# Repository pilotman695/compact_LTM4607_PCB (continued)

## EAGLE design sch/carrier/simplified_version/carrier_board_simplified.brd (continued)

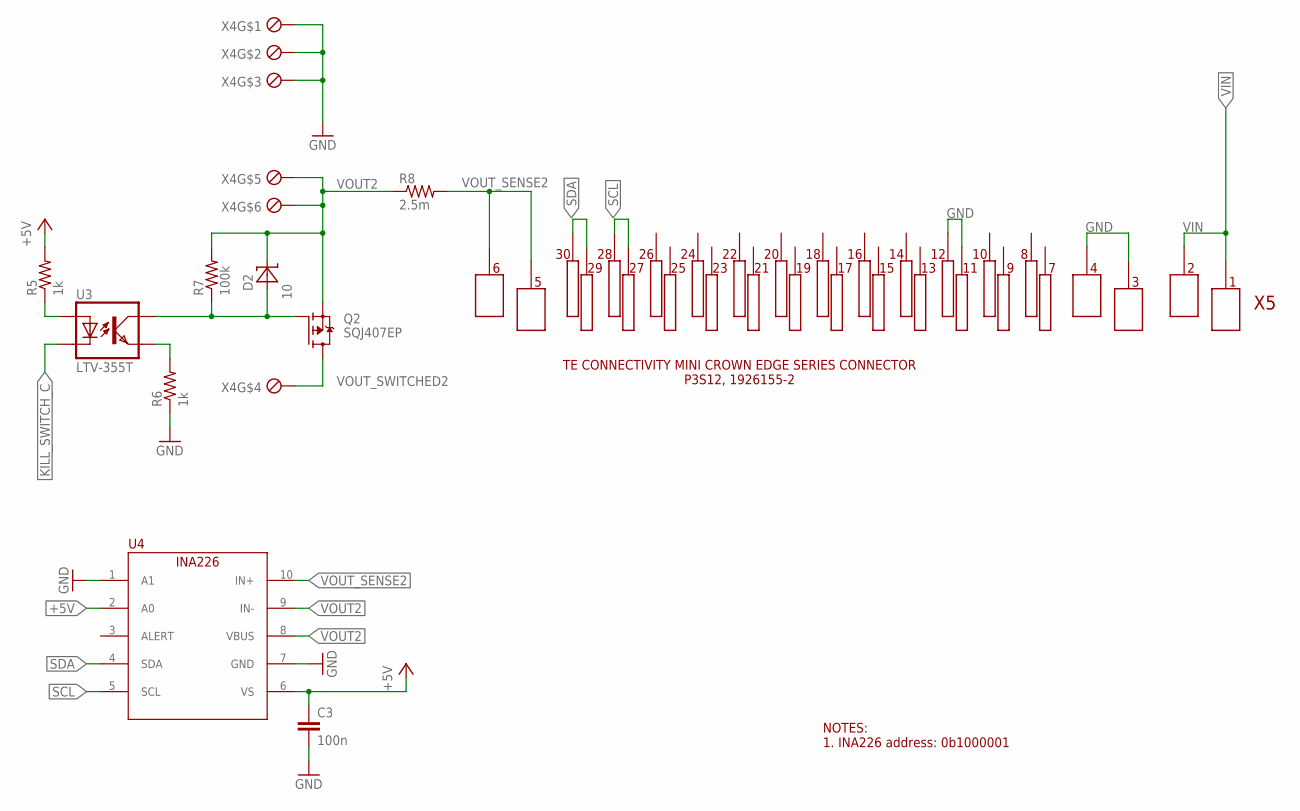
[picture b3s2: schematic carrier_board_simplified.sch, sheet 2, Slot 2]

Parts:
C3: 100n; C0603
D2: 10; SOD123
Q2: SQJ407EP; POWERPAK_SO8L_SINGLE
R5, R6: 1k; R0603
R7: 100k; R0603
R8: 2.5m; R2512
U3: LTV-355T; SMD4
U4: INA226; MSOP10
X4: 284391-6
X5: 1926155-2_SOCK

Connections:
+5V: C3.1, R5.2, U4.2 (A0), U4.6 (VS); also elsewhere on the board
GATE_VOUT2: D2.2 (A), Q2.P$4 (G), R7.1, U3.COLLECTOR (COL)
GND: C3.2, R6.1, U4.1 (A1), U4.7 (GND), X4.P$1, X4.P$2, X4.P$3, X5.P$3_1, X5.P$3_2, X5.P$3_3, X5.P$4_1, X5.P$4_2, X5.P$4_3, X5.P$11, X5.P$12; also elsewhere on the board
KILL_SWITCH_C: U3.CATHODE (C); also elsewhere on the board
unnamed: R6.2, U3.EMITTER (EMIT)
unnamed: R5.1, U3.ANODE (A)
SCL: U4.5 (SCL), X5.P$27, X5.P$28; also elsewhere on the board
SDA: U4.4 (SDA), X5.P$29, X5.P$30; also elsewhere on the board
VIN: X5.P$1_1, X5.P$1_2, X5.P$1_3, X5.P$2_1, X5.P$2_2, X5.P$2_3; also elsewhere on the board
VOUT2: D2.1 (C), Q2.P$1 (S), Q2.P$2 (S), Q2.P$3 (S), R7.2, R8.1, U4.8 (VBUS), U4.9 (IN-), X4.P$5, X4.P$6
VOUT_SENSE2: R8.2, U4.10 (IN+), X5.P$5_1, X5.P$5_2, X5.P$5_3, X5.P$6_1, X5.P$6_2, X5.P$6_3
VOUT_SWITCHED2: Q2.P$5 (D), Q2.P$6 (D), Q2.P$7 (D), Q2.P$8 (D), X4.P$4

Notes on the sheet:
NOTES: 1. INA226 address: 0b1000001

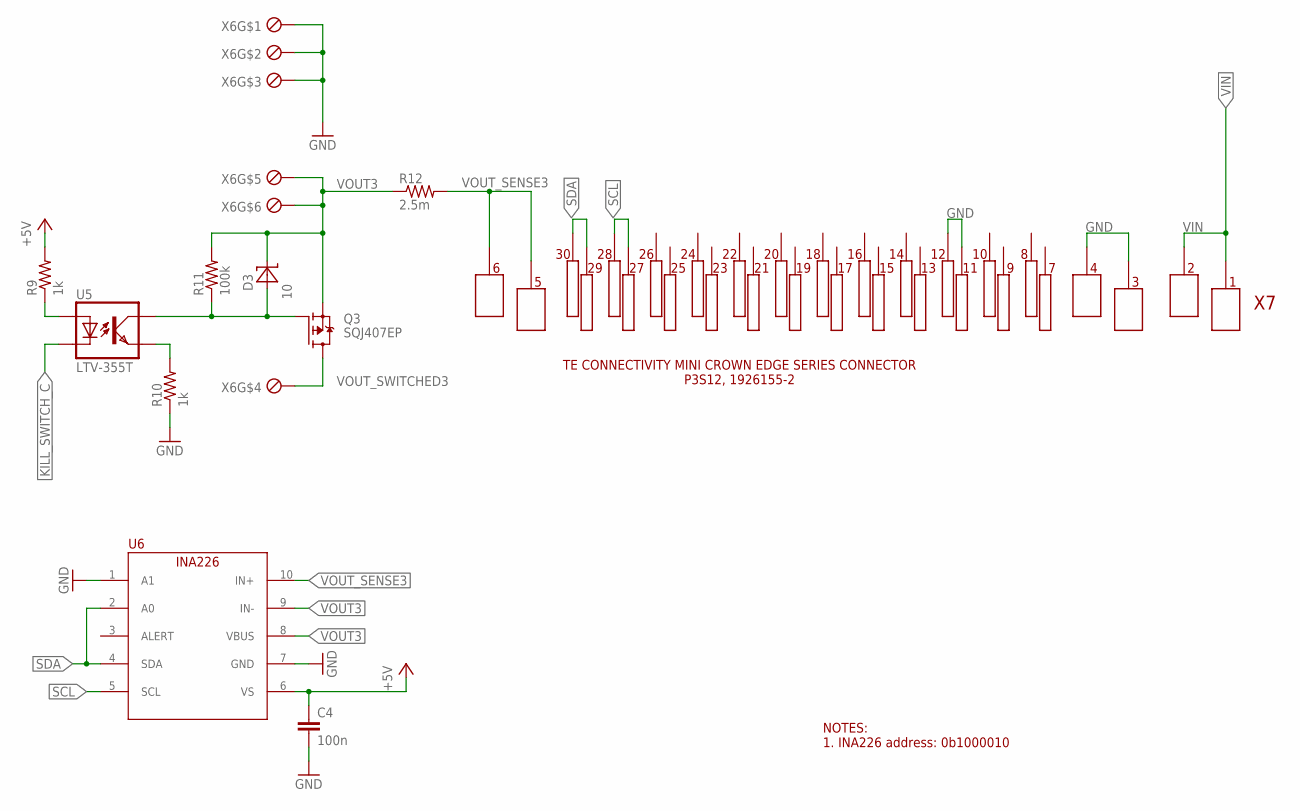
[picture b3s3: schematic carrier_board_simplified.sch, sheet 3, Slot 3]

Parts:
C4: 100n; C0603
D3: 10; SOD123
Q3: SQJ407EP; POWERPAK_SO8L_SINGLE
R9, R10: 1k; R0603
R11: 100k; R0603
R12: 2.5m; R2512
U5: LTV-355T; SMD4
U6: INA226; MSOP10
X6: 284391-6
X7: 1926155-2_SOCK

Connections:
+5V: C4.1, R9.2, U6.6 (VS); also elsewhere on the board
GATE_VOUT3: D3.2 (A), Q3.P$4 (G), R11.1, U5.COLLECTOR (COL)
GND: C4.2, R10.1, U6.1 (A1), U6.7 (GND), X6.P$1, X6.P$2, X6.P$3, X7.P$3_1, X7.P$3_2, X7.P$3_3, X7.P$4_1, X7.P$4_2, X7.P$4_3, X7.P$11, X7.P$12; also elsewhere on the board
KILL_SWITCH_C: U5.CATHODE (C); also elsewhere on the board
unnamed: R10.2, U5.EMITTER (EMIT)
unnamed: R9.1, U5.ANODE (A)
SCL: U6.5 (SCL), X7.P$27, X7.P$28; also elsewhere on the board
SDA: U6.2 (A0), U6.4 (SDA), X7.P$29, X7.P$30; also elsewhere on the board
VIN: X7.P$1_1, X7.P$1_2, X7.P$1_3, X7.P$2_1, X7.P$2_2, X7.P$2_3; also elsewhere on the board
VOUT3: D3.1 (C), Q3.P$1 (S), Q3.P$2 (S), Q3.P$3 (S), R11.2, R12.1, U6.8 (VBUS), U6.9 (IN-), X6.P$5, X6.P$6
VOUT_SENSE3: R12.2, U6.10 (IN+), X7.P$5_1, X7.P$5_2, X7.P$5_3, X7.P$6_1, X7.P$6_2, X7.P$6_3
VOUT_SWITCHED3: Q3.P$5 (D), Q3.P$6 (D), Q3.P$7 (D), Q3.P$8 (D), X6.P$4

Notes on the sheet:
NOTES: 1. INA226 address: 0b1000010

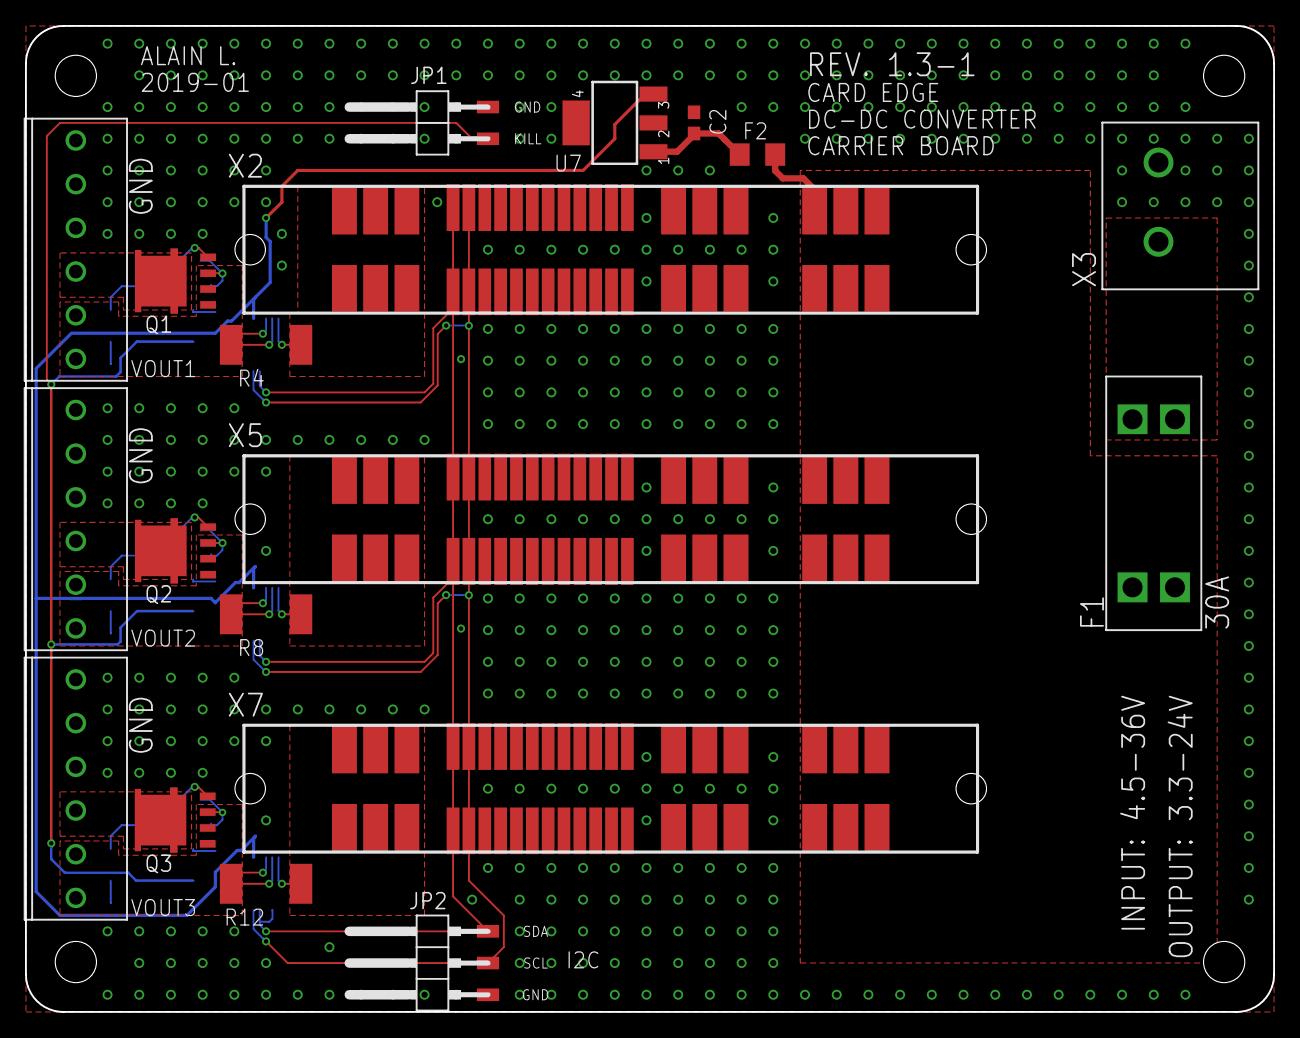
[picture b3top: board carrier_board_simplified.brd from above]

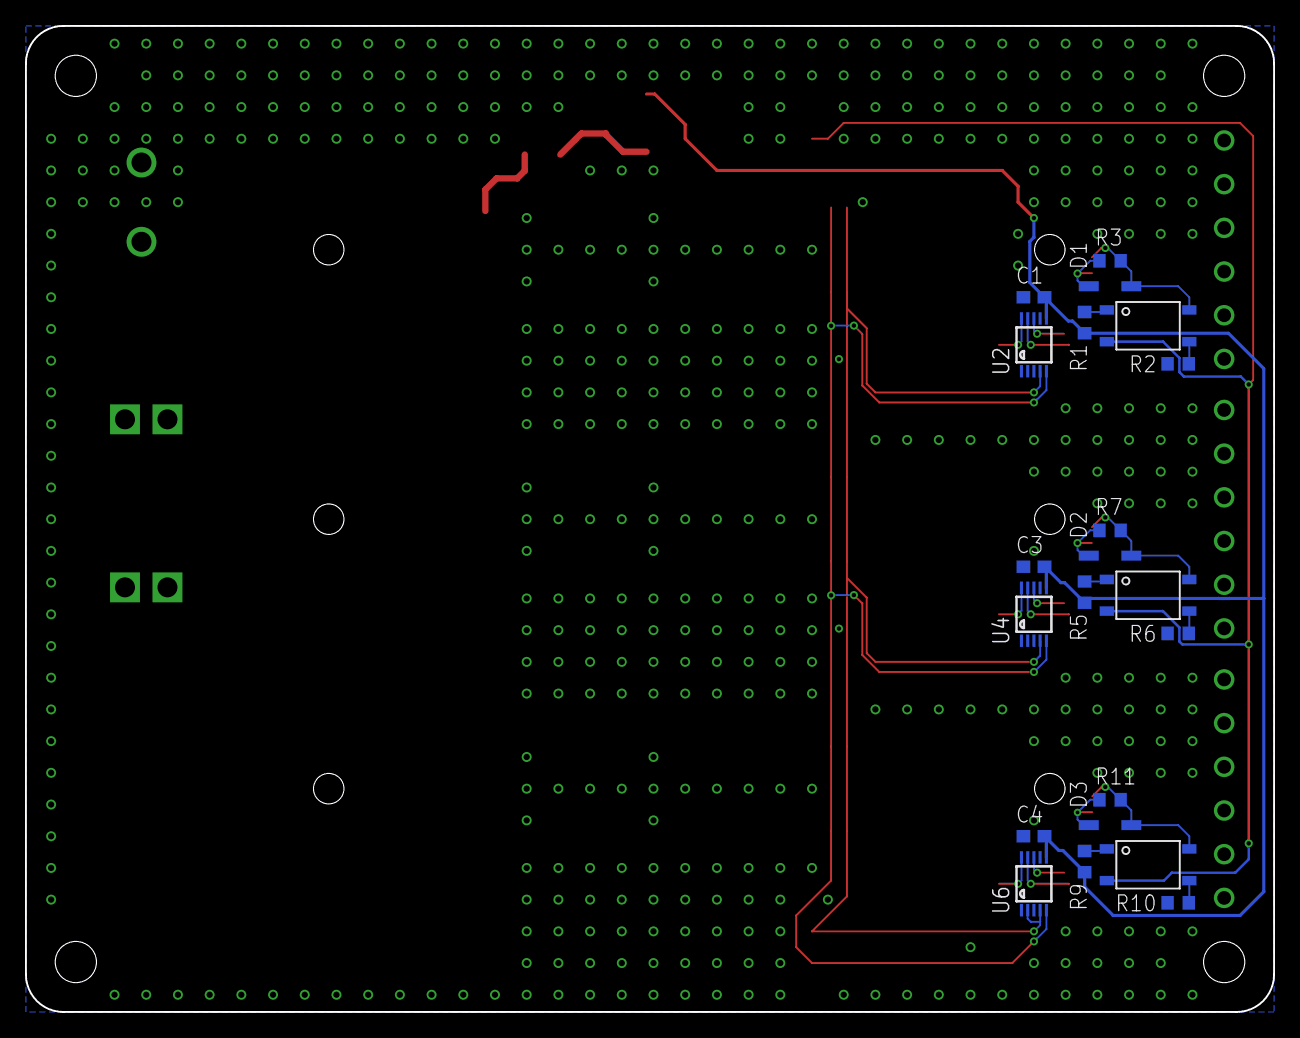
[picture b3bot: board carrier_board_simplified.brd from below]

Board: 2 copper layers, 100.0 x 79.0 mm, 45 parts (21 on the bottom side), 26 nets.

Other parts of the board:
U$1, U$2, U$3, U$4: STAND-OFF
U$5: A4L-LOC

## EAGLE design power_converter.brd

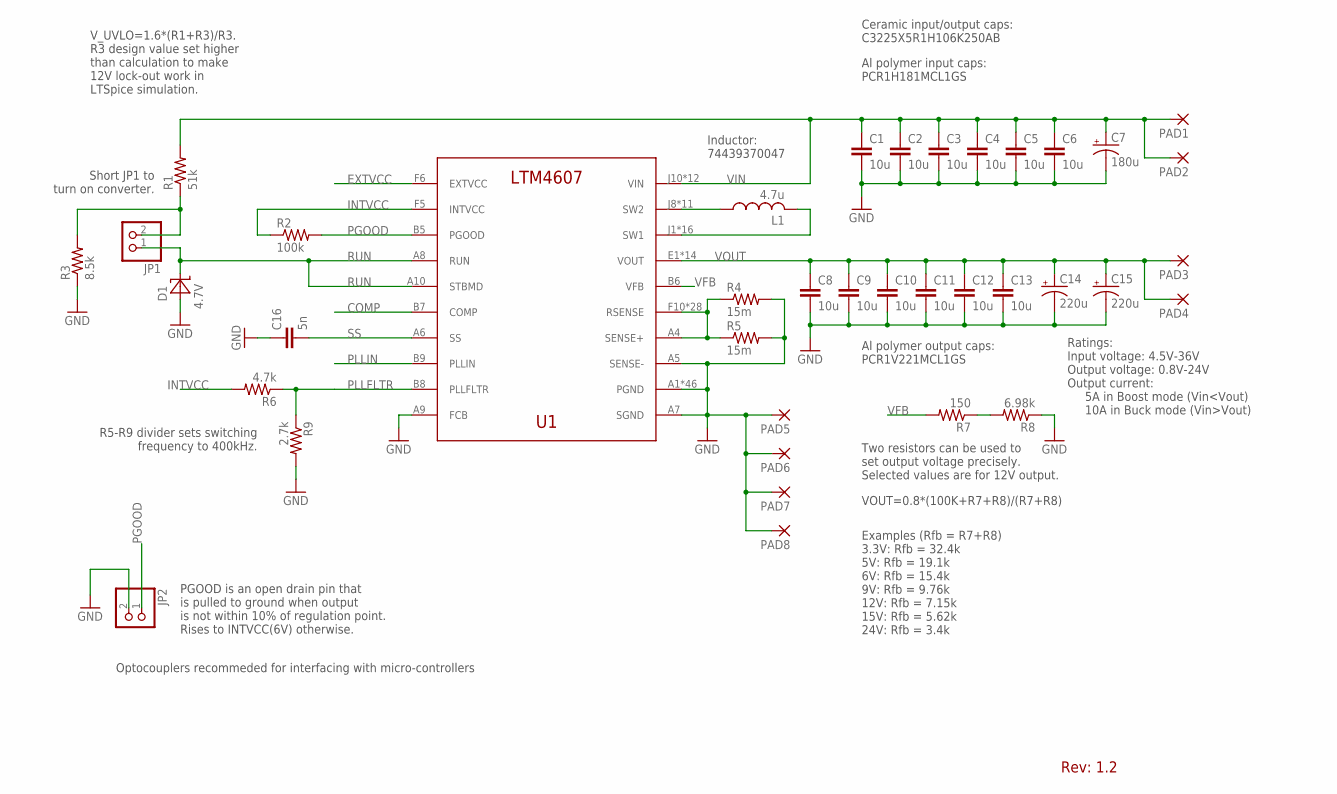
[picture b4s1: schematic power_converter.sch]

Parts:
C1, C2, C3, C4, C5, C6, C8, C9, C10, C11, C12, C13: 10u; C1210
C7: 180u; PCR1H181MCL1GS
C14, C15: 220u; PCR1V221MCL1GS
C16: 5n; C0603
D1: 4.7V; SOT23
JP1, JP2: PINHD-1X02_2.54-SMD; 1X02SMD
L1: 4.7u; 74439370047
PAD1, PAD2, PAD3, PAD4, PAD5, PAD6, PAD7, PAD8: 3,81/1,5
R1: 51k; R0603
R2: 100k; R0603
R3: 8.5k; R0603
R4, R5: 15m; R1206
R6: 4.7k; R0603
R7: 150; R0603
R8: 6.98k; R0603
R9: 2.7k; R0603
U1: LTM4607EVPBF; LGA-141

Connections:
COMP: U1.B7 (COMP)
EXTVCC: U1.F6 (EXTVCC)
GND: C1.2, C2.2, C3.2, C4.2, C5.2, C6.2, C7.NEG (-), C8.2, C9.2, C10.2, C11.2, C12.2, C13.2, C14.NEG (-), C15.NEG (-), C16.1, D1.1 (A), JP2.2, PAD5.1, PAD6.1, PAD7.1, PAD8.1, R3.1, R4.2, R5.2, R8.1, R9.2, U1.A1 (PGND), U1.A2 (PGND), U1.A3 (PGND), U1.A5 (SENSE-), U1.A7 (SGND), U1.A9 (FCB), U1.A11 (PGND), U1.A12 (PGND), U1.B1 (PGND), U1.B2 (PGND), U1.B3 (PGND), U1.B4 (PGND), U1.B10 (PGND), U1.B11 (PGND), U1.B12 (PGND), U1.C1 (PGND), U1.C2 (PGND), U1.C3 (PGND), U1.C4 (PGND), U1.C5 (PGND), U1.C6 (PGND), U1.C7 (PGND), U1.C8 (PGND), U1.C9 (PGND), U1.C10 (PGND), U1.C11 (PGND), U1.C12 (PGND), U1.D1 (PGND), U1.D2 (PGND), U1.D3 (PGND), U1.D4 (PGND), U1.D5 (PGND), U1.D6 (PGND), U1.D7 (PGND), U1.D8 (PGND), U1.D9 (PGND), U1.D10 (PGND), U1.D11 (PGND), U1.D12 (PGND), U1.E3 (PGND), U1.E4 (PGND), U1.E5 (PGND), U1.E6 (PGND), U1.E7 (PGND), U1.E8 (PGND), U1.E9 (PGND), U1.E10 (PGND), U1.E11 (PGND), U1.E12 (PGND)
INTVCC: R2.1, R6.2, U1.F5 (INTVCC)
unnamed: R7.1, R8.2
unnamed: JP1.2, R1.1, R3.2
PGOOD: JP2.1, R2.2, U1.B5 (PGOOD)
PLLFLTR: R6.1, R9.1, U1.B8 (PLLFLTR)
PLLIN: U1.B9 (PLLIN)
RSENSE: R4.1, R5.1, U1.A4 (SENSE+), U1.F10 (RSENSE), U1.F11 (RSENSE), U1.F12 (RSENSE), U1.G5 (RSENSE), U1.G6 (RSENSE), U1.G7 (RSENSE), U1.G8 (RSENSE), U1.G9 (RSENSE), U1.G10 (RSENSE), U1.G11 (RSENSE), U1.G12 (RSENSE), U1.H5 (RSENSE), U1.H6 (RSENSE), U1.H7 (RSENSE), U1.H8 (RSENSE), U1.H9 (RSENSE), U1.H10 (RSENSE), U1.H11 (RSENSE), U1.H12 (RSENSE), U1.J5 (RSENSE), U1.J6 (RSENSE), U1.J7 (RSENSE), U1.K5 (RSENSE), U1.K6 (RSENSE), U1.L5 (RSENSE), U1.L6 (RSENSE), U1.M5 (RSENSE), U1.M6 (RSENSE)
RUN: D1.3 (C), JP1.1, U1.A8 (RUN), U1.A10 (STBMD)
SS: C16.2, U1.A6 (SS)
SW1: L1.M2 (2), U1.J1 (SW1), U1.J2 (SW1), U1.J3 (SW1), U1.J4 (SW1), U1.K1 (SW1), U1.K2 (SW1), U1.K3 (SW1), U1.K4 (SW1), U1.L1 (SW1), U1.L2 (SW1), U1.L3 (SW1), U1.L4 (SW1), U1.M1 (SW1), U1.M2 (SW1), U1.M3 (SW1), U1.M4 (SW1)
SW2: L1.M1 (1), U1.J8 (SW2), U1.J9 (SW2), U1.K7 (SW2), U1.K8 (SW2), U1.K9 (SW2), U1.L7 (SW2), U1.L8 (SW2), U1.L9 (SW2), U1.M7 (SW2), U1.M8 (SW2), U1.M9 (SW2)
VFB: R7.2, U1.B6 (VFB)
VIN: C1.1, C2.1, C3.1, C4.1, C5.1, C6.1, C7.POS (+), PAD1.1, PAD2.1, R1.2, U1.J10 (VIN), U1.J11 (VIN), U1.J12 (VIN), U1.K10 (VIN), U1.K11 (VIN), U1.K12 (VIN), U1.L10 (VIN), U1.L11 (VIN), U1.L12 (VIN), U1.M10 (VIN), U1.M11 (VIN), U1.M12 (VIN)
VOUT: C8.1, C9.1, C10.1, C11.1, C12.1, C13.1, C14.POS (+), C15.POS (+), PAD3.1, PAD4.1, U1.E1 (VOUT), U1.E2 (VOUT), U1.F1 (VOUT), U1.F2 (VOUT), U1.F3 (VOUT), U1.F4 (VOUT), U1.G1 (VOUT), U1.G2 (VOUT), U1.G3 (VOUT), U1.G4 (VOUT), U1.H1 (VOUT), U1.H2 (VOUT), U1.H3 (VOUT), U1.H4 (VOUT)

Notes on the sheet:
Ceramic input/output caps: C3225X5R1H106K250AB
Al polymer input caps: PCR1H181MCL1GS
Al polymer output caps: PCR1V221MCL1GS
Two resistors can be used to set output voltage precisely. Selected values are for 12V output.
VOUT=0.8*(100K+R7+R8)/(R7+R8)
V_UVLO=1.6*(R1+R3)/R3. R3 design value set higher than calculation to make 12V lock-out work in LTSpice simulation.
Short JP1 to turn on converter.
R5-R9 divider sets switching frequency to 400kHz.
PGOOD is an open drain pin that is pulled to ground when output is not within 10% of regulation point. Rises to INTVCC(6V) otherwise.
Examples (Rfb = R7+R8) 3.3V: Rfb = 32.4k 5V: Rfb = 19.1k 6V: Rfb = 15.4k 9V: Rfb = 9.76k 12V: Rfb = 7.15k 15V: Rfb = 5.62k 24V: Rfb = 3.4k
Ratings: Input voltage: 4.5V-36V Output voltage: 0.8V-24V Output current: 5A in Boost mode (Vin<Vout) 10A in Buck mode (Vin>Vout)
Optocouplers recommeded for interfacing with micro-controllers
Inductor: 74439370047
Rev: 1.2

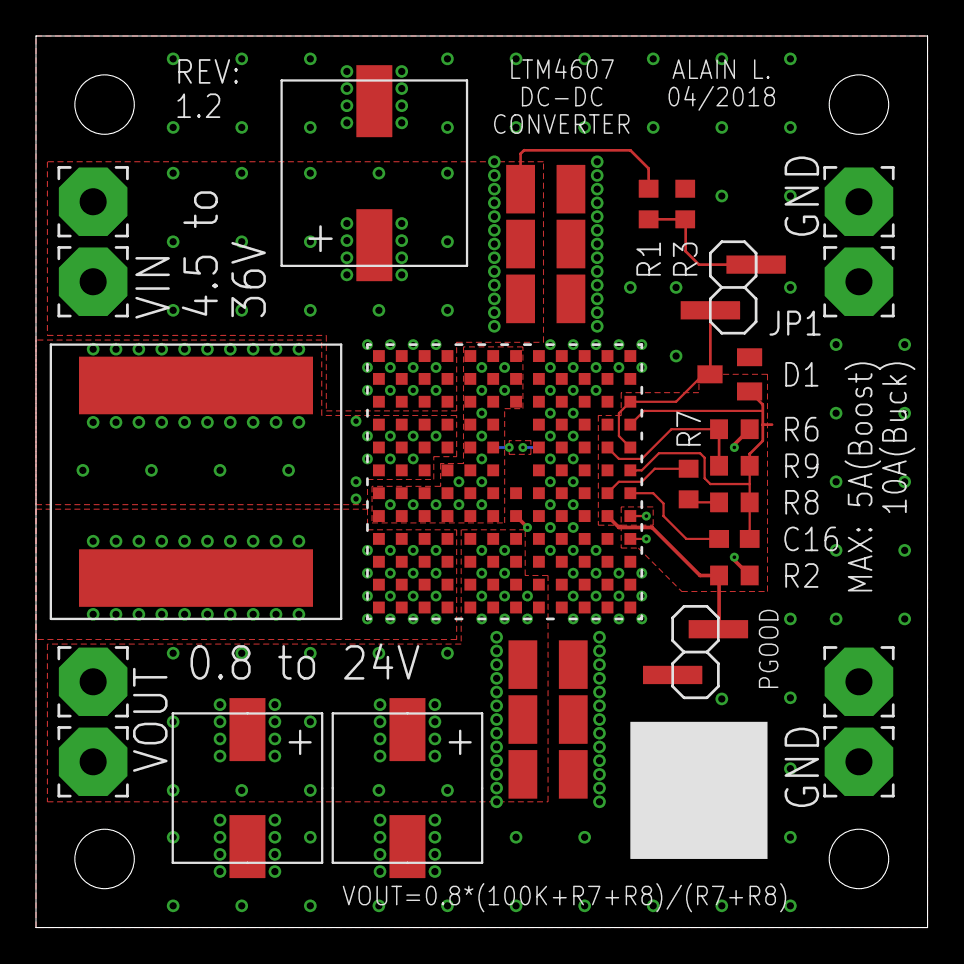
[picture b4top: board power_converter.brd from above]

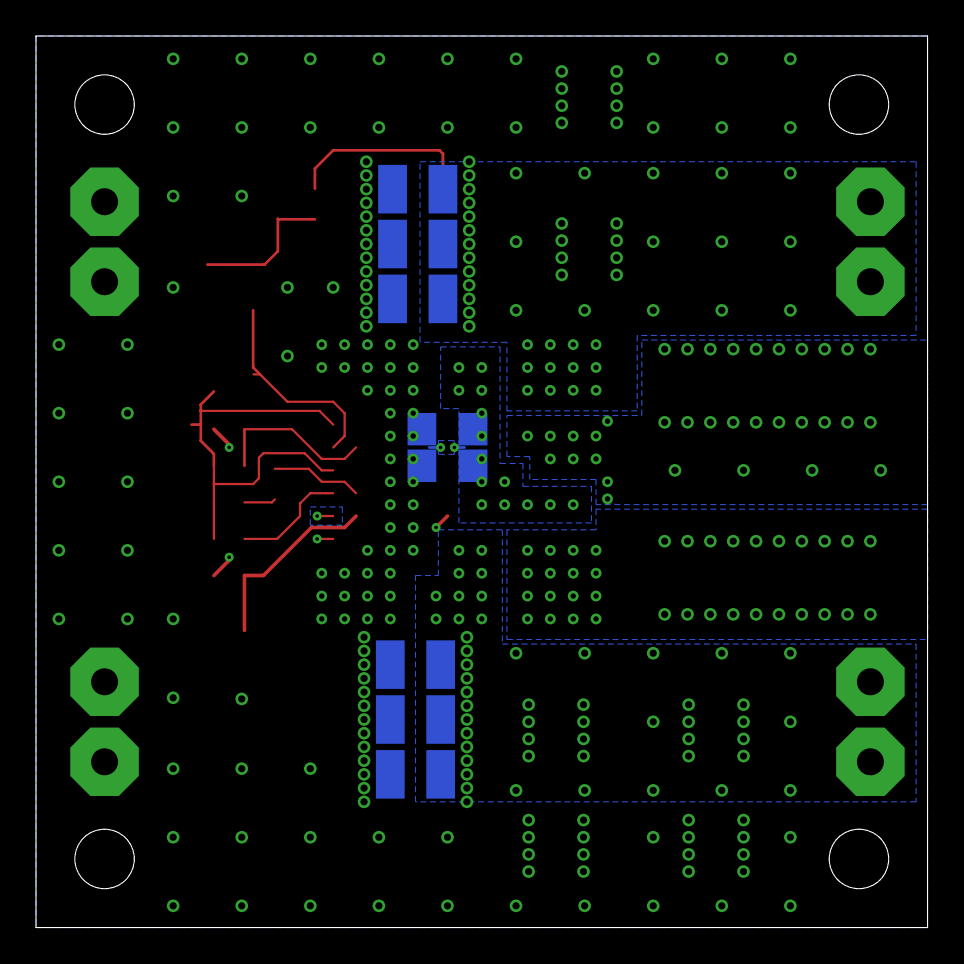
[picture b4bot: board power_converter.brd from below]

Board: 4 copper layers, 49.5 x 49.5 mm, 43 parts (8 on the bottom side), 14 nets.

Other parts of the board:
U$1, U$2, U$3, U$4: STAND-OFF
U$5: A4L-LOC

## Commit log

2018-04-21 Laid out and routed power components
2018-04-21 update license
2018-04-26 Completed revision 1.0
2018-04-26 Split current sense resistor into two; Added BOM and LTSpice simulation
2018-04-26 Added CAM files; Increased wirepad drill; Added more vias
2018-05-09 fixed typo in .sch
2018-05-10 Reduced stencil hole size for LTM4607 to reduce odds of solder bridging
2018-07-16 Restructured files
2018-09-27 Version 2
2018-10-06 Carrier board
2018-10-06 Updated pdf
2018-10-06 added simulation
2018-10-28 Added carrier BOM; Chaned carrier MOSFETs
2018-10-28 Added CAM files
2018-10-28 Updated CAM files
2018-12-09 Revision 1.2
2018-12-15 Carrier rev. 1.3
2018-12-27 Fixed typo in sch
2018-12-27 Added missing via
2019-01-04 Simplified low-cost version 1.3-1 added
2019-10-14 Carrier rev. 1.4
